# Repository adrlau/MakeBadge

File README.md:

# MakeBadge
a badge / ghost guts for make ntnu.

based on the haloween diagram made 2021
will feature pcb and 3d models.

current progress
(https://user-images.githubusercontent.com/25004152/155996012-b5a18ea0-fdf4-4a80-84d6-8b9fef0d11e9.png)

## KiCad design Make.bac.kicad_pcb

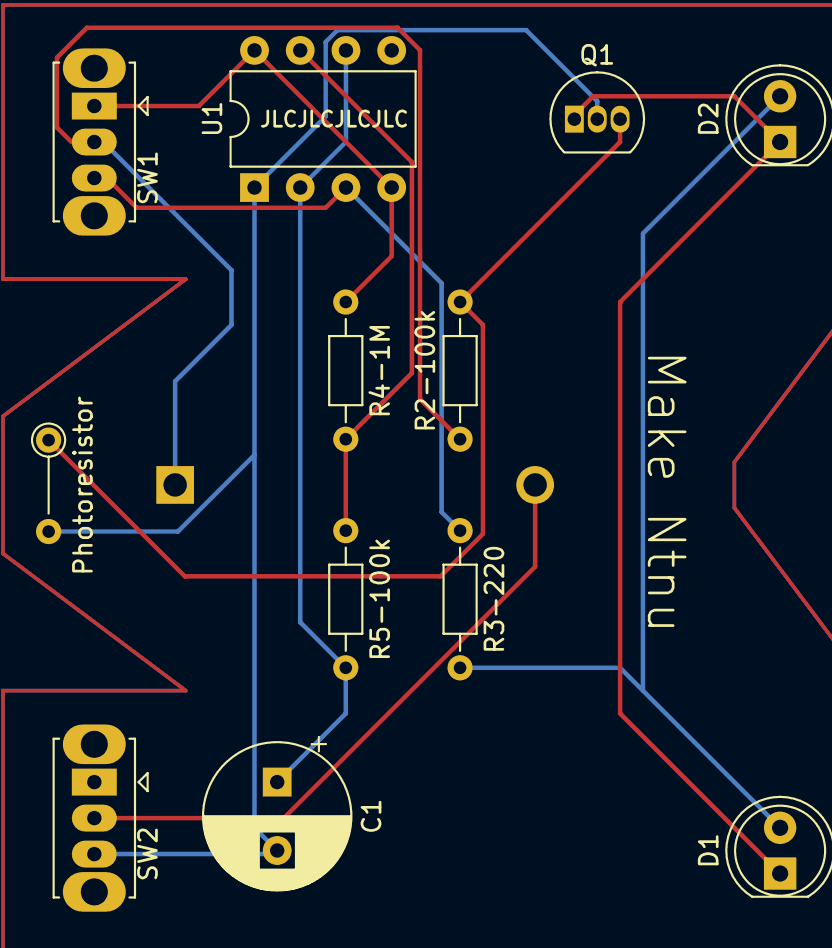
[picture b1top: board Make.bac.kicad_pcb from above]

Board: 2 copper layers, 13 parts (1 on the bottom side), 10 nets.

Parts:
BT1: Battery_Cell; BatteryHolder_ComfortableElectronic_CH273-2450_1x2450
C1: C0.1; CP_Radial_D8.0mm_P3.80mm
D1, D2: LED; LED_D5.0mm
Photoresistor: R_Photo; R_Axial_DIN0204_L3.6mm_D1.6mm_P5.08mm_Vertical
Q1: BC240; TO-92_Inline
R2-100k, R5-100k: R100k; R_Axial_DIN0204_L3.6mm_D1.6mm_P7.62mm_Horizontal
R3-220: R220; R_Axial_DIN0204_L3.6mm_D1.6mm_P7.62mm_Horizontal
R4-1M: R1M; R_Axial_DIN0204_L3.6mm_D1.6mm_P7.62mm_Horizontal
SW1, SW2: SW_SPDT; SW_Slide_1P2T_CK_OS102011MS2Q
U1: TLC555xP; DIP-8_W7.62mm

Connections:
unnamed: BT1.1 (+), R2-100k.1, SW1.2 (B)
unnamed: BT1.2 (-), SW2.2 (B)
unnamed: C1.1, R5-100k.2, U1.2 (TR), U1.6 (THR)
unnamed: C1.2, Photoresistor.2, Q1.2 (E), SW2.3 (C), U1.1 (GND)
unnamed: Photoresistor.1, Q1.3 (B), R2-100k.2
unnamed: D1.1 (K), D2.1 (K), Q1.1 (C)
unnamed: D1.2 (A), D2.2 (A), R3-220.2
unnamed: R4-1M.1, SW1.1 (A), U1.4 (R), U1.8 (VCC)
unnamed: R4-1M.2, R5-100k.1, U1.7 (DIS)
unnamed: R3-220.1, SW1.3 (C), U1.3 (Q)

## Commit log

2022-02-26 added baseline files.
